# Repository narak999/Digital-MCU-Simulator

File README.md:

# Digital-MCU-Simulator
This is the project for ECEN 403 and ECEN 404 class.

For my code (DMCUS_IDE.py), in order to successfully run it, the user will need to change the directories inside the code. The user will also need to install some Python packages including Pygments, Tkinter, Signal, Subprocess, and Webbrowser. One more thing that might prevent the code from running on the user's computer might be the location of the icon file cannot be located, although the icon file is attached with the code above. 

simavr was created by Michel Polet under the GNU GPL 3.0 licensing. His github can be found here:
https://github.com/buserror/simavr

NOTE: This Python code is created and meant to run with Python 3.6. Using a different version of Python to compile and run the code might cause unexpected errors.

Compilation command for simavr: 

avr-gcc -Wall -gdwarf-2 -Os -std=gnu99 -DF_CPU=8000000 -fno-inline-small-functions -ffunction-sections -fdata-sections -Wl,--relax,--gc-sections -Wl,--undefined=_mmcu,--section-start=.mmcu=0x910000 -I ~/Desktop/simavr/simavr/sim -I ~/Desktop/simavr/simavr/sim/avr -mmcu=atmega88 ledblink.c -o ledblink.elf

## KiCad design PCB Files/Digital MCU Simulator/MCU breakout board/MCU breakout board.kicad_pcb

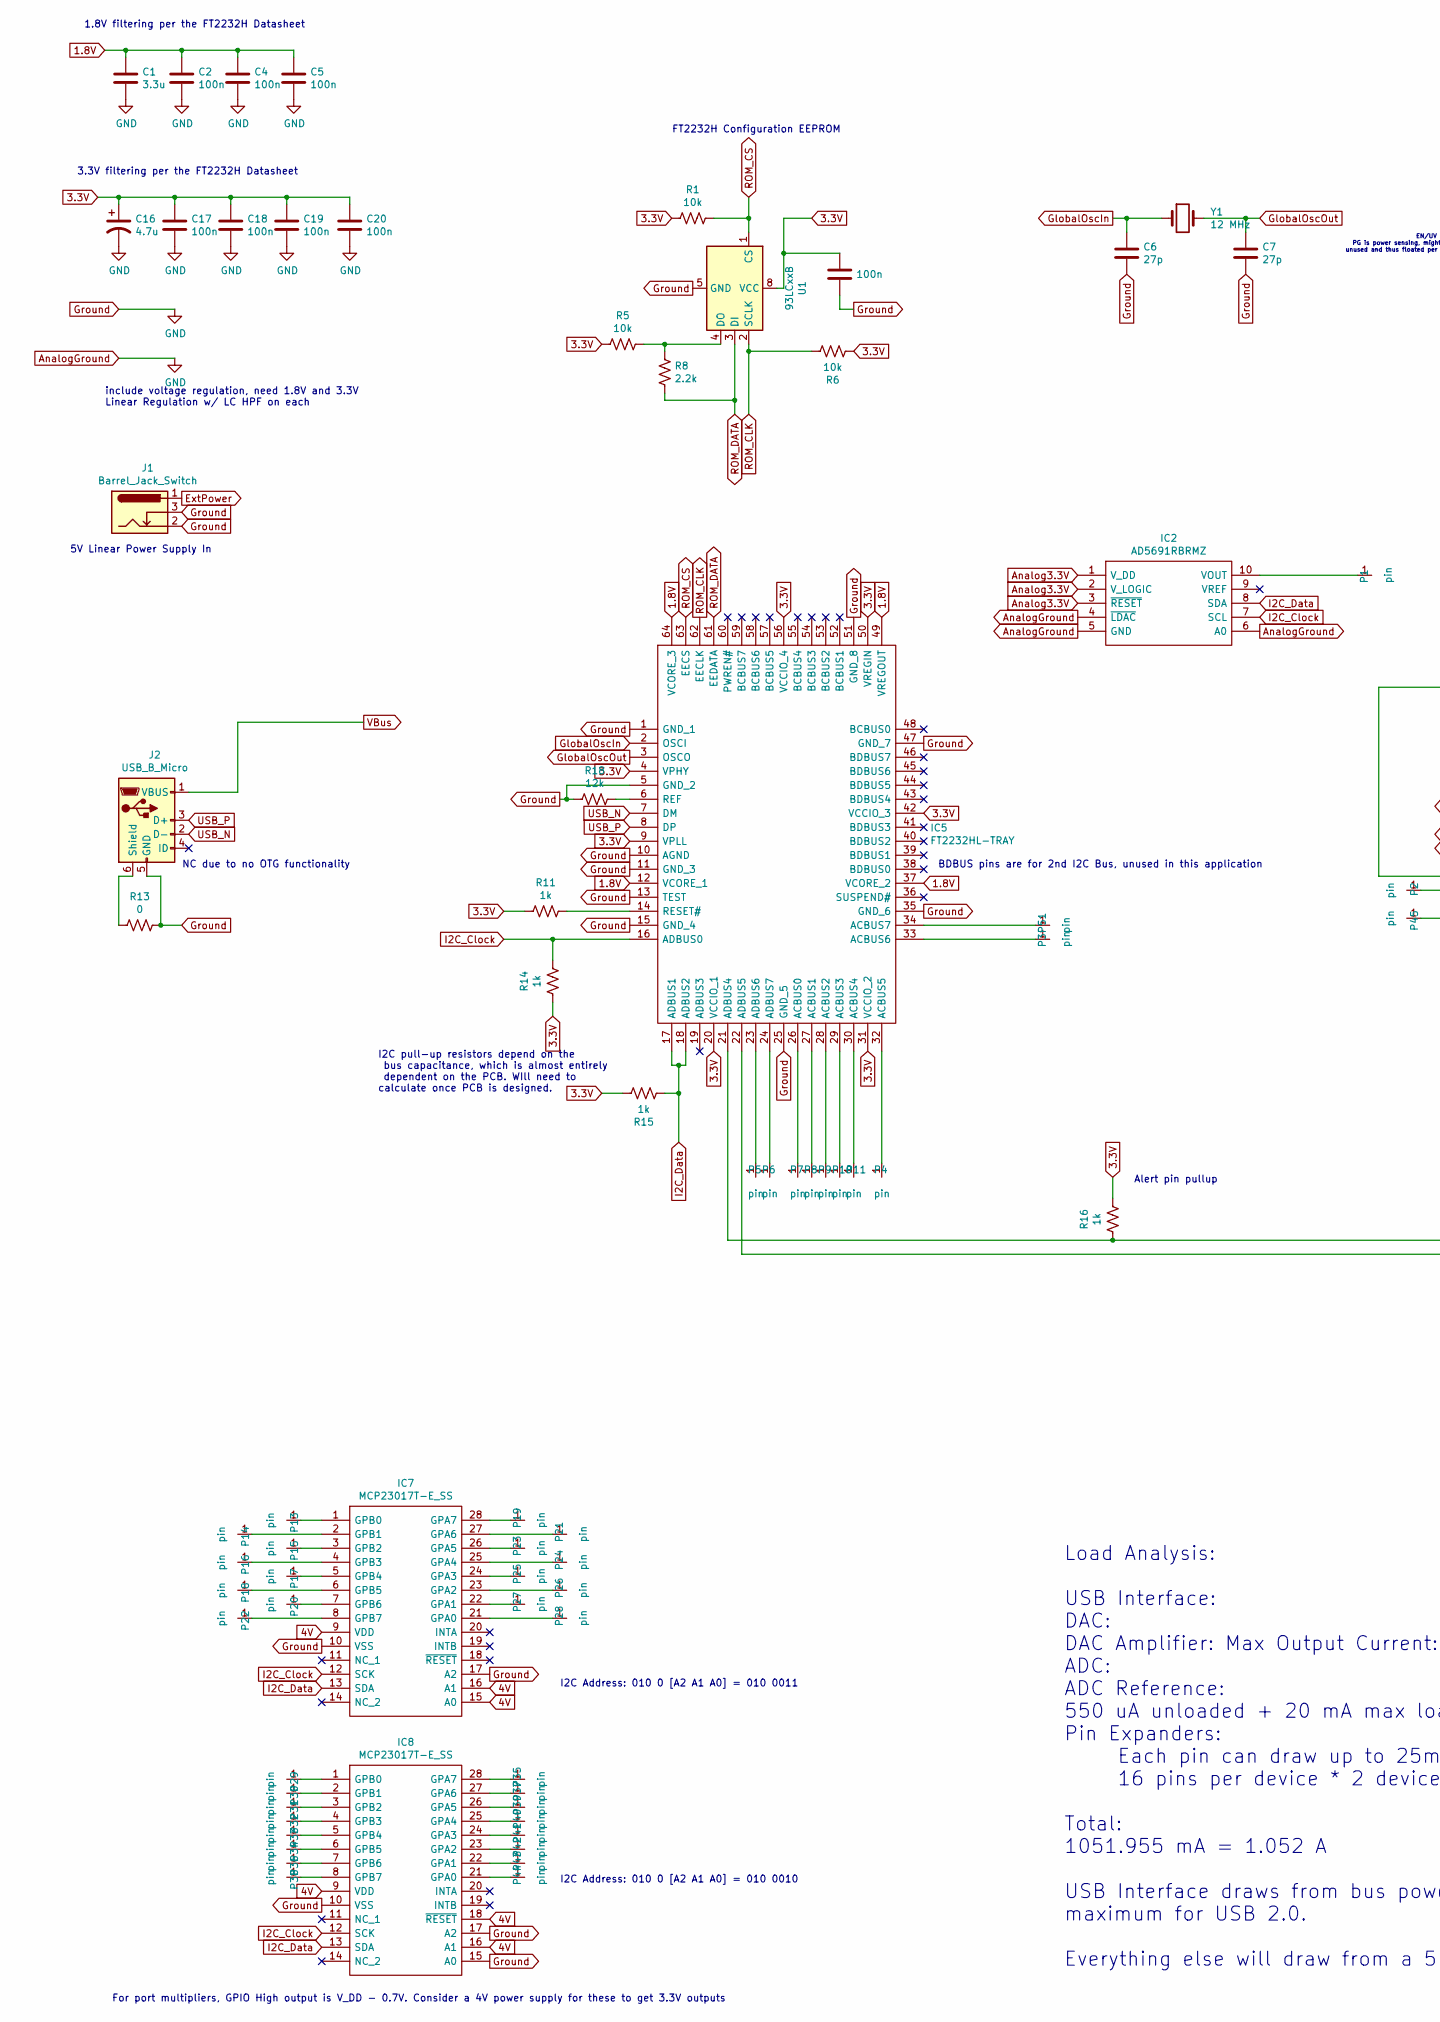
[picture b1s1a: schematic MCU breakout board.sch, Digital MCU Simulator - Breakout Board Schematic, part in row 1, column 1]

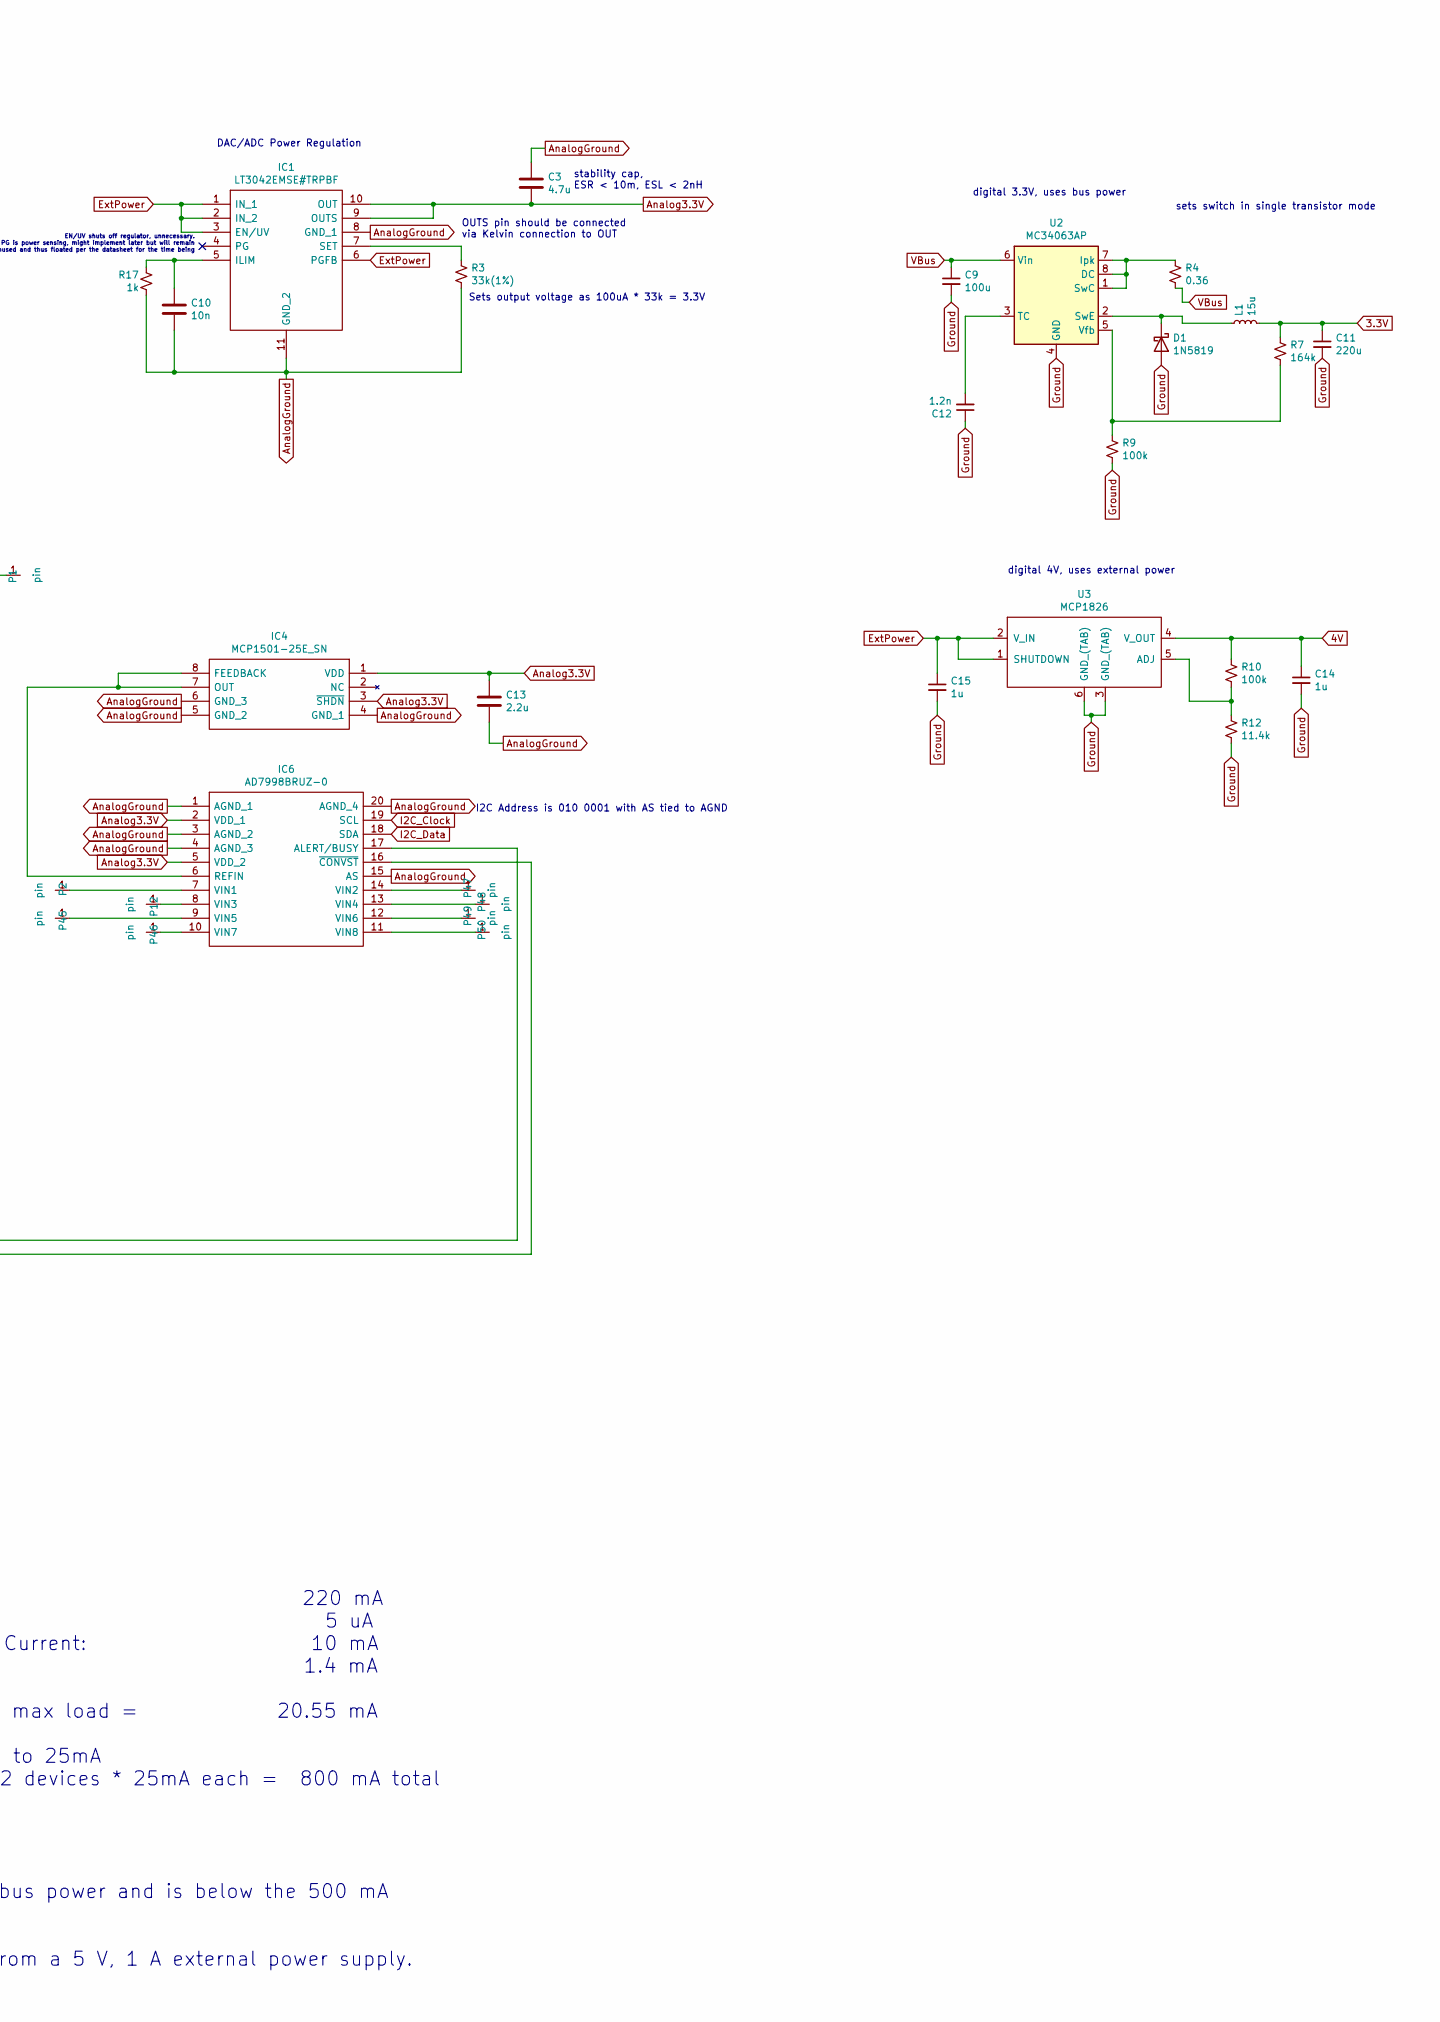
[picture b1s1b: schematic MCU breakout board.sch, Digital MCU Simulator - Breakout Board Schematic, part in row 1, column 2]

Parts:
C1: 3.3u; C_0805_2012Metric
C2, C4, C5, C8, C17, C18, C19, C20: 100n; C_0805_2012Metric
C3: 4.7u; C_0805_2012Metric
C6, C7: 27p; C_0805_2012Metric
C9: 100u; C_0805_2012Metric
C10: 10n; C_0805_2012Metric
C11: 220u; C_1210_3225Metric
C12: 1.2n; C_0805_2012Metric
C13: 2.2u; C_0805_2012Metric
C14, C15: 1u; C_0805_2012Metric
C16: 4.7u; CP_Elec_6.3x5.8
D1: 1N5819; D_DO-41_SOD81_P10.16mm_Horizontal
IC1: LT3042EMSE#TRPBF; SOP50P490X110-11N; Mouser Part Number 584-LT3042EMSE#TRPBF
IC2: AD5691RBRMZ; SOP50P490X110-10N; Manufacturer_Part_Number AD5691RBRMZ
IC4: MCP1501-25E_SN; SOIC127P600X175-8N; Mouser Part Number 579-MCP1501-25E/SN
IC5: FT2232HL-TRAY; QFP50P1200X1200X160-64N; Mouser Part Number 895-FT2232HL-TRAY
IC6: AD7998BRUZ-0; SOP65P640X120-20N; Mouser Part Number 584-AD7998BRUZ-0
IC7, IC8: MCP23017T-E_SS; SOP65P780X200-28N; Mouser Part Number 579-MCP23017T-E/SS
J1: Barrel_Jack_Switch; BarrelJack_CUI_PJ-102AH_Horizontal
J2: USB_B_Micro; USB_Micro-B_Molex-105017-0001
L1: 15u; L_1812_4532Metric
P1, P2, P3, P4, P5, P6, P7, P8, P9, P10, P11, P12, P13, P14, P15, P16, P17, P18, P19, P20, P21, P22, P23, P24, P25, P26, P27, P28, P29, P30, P31, P32, P33, P34, P35, P36, P37, P38, P39, P40, P41, P42, P43, P44, P45, P46, P47, P48, P49, P50, P51: pin; PinHeader_1x01_P2.54mm_Vertical
R1, R5, R6: 10k; R_0805_2012Metric
R3: 33k(1%); R_0805_2012Metric
R4: 0.36; R_0805_2012Metric
R7: 164k; R_0805_2012Metric
R8: 2.2k; R_0805_2012Metric
R9, R10: 100k; R_0805_2012Metric
R11, R14, R15, R16, R17: 1k; R_0805_2012Metric
R12: 11.4k; R_0805_2012Metric
R13: 0; R_0805_2012Metric
R18: 12k; R_0805_2012Metric
U1: 93LCxxB; SOIC-8_3.9x4.9mm_P1.27mm
U2: MC34063AP; DIP-8_W7.62mm
U3: MCP1826; TO-220-5_Horizontal_TabDown_tab_pin_6
Y1: 12 MHz; Crystal_HC49-U_Vertical

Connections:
1.8V: C1.1, C2.1, C4.1, C5.1, IC5.12 (VCORE_1), IC5.37 (VCORE_2), IC5.49 (VREGOUT), IC5.64 (VCORE_3)
3.3V: C8.1, C11.1, C16.1, C17.1, C18.1, C19.1, C20.1, IC5.4 (VPHY), IC5.9 (VPLL), IC5.20 (VCCIO_1), IC5.31 (VCCIO_2), IC5.42 (VCCIO_3), IC5.50 (VREGIN), IC5.56 (VCCIO_4), L1.2, R1.2, R5.2, R6.2, R7.1, R11.2, R14.2, R15.1, R16.1, U1.8 (VCC)
4V: C14.1, IC7.9 (VDD), IC7.15 (A0), IC7.16 (A1), IC8.9 (VDD), IC8.16 (A1), IC8.18 (~RESET), R10.1, U3.4 (V_OUT)
Analog3.3V: C3.2, C13.1, IC1.9 (OUTS), IC1.10 (OUT), IC2.1 (V_DD), IC2.2 (V_LOGIC), IC2.3 (~RESET), IC4.1 (VDD), IC4.3 (~SHDN), IC6.2 (VDD_1), IC6.5 (VDD_2)
AnalogGround: C1.2, C2.2, C3.1, C4.2, C5.2, C6.2, C7.2, C8.2, C9.2, C10.2, C11.2, C12.1, C13.2, C14.2, C15.2, C16.2, C17.2, C18.2, C19.2, C20.2, D1.2 (A), IC1.8 (GND_1), IC1.11 (GND_2), IC2.4 (~LDAC), IC2.5 (GND), IC2.6 (A0), IC4.4 (GND_1), IC4.5 (GND_2), IC4.6 (GND_3), IC5.1 (GND_1), IC5.5 (GND_2), IC5.10 (AGND), IC5.11 (GND_3), IC5.13 (TEST), IC5.15 (GND_4), IC5.25 (GND_5), IC5.35 (GND_6), IC5.47 (GND_7), IC5.51 (GND_8), IC6.1 (AGND_1), IC6.3 (AGND_2), IC6.4 (AGND_3), IC6.15 (AS), IC6.20 (AGND_4), IC7.10 (VSS), IC7.17 (A2), IC8.10 (VSS), IC8.15 (A0), IC8.17 (A2), J1.2, J1.3, J2.5 (GND), R3.2, R9.2, R12.2, R13.1, R17.2, R18.2, U1.5 (GND), U2.4 (GND), U3.3 (GND_(TAB)), U3.6 (GND_(TAB)); also elsewhere on the board
ExtPower: C15.1, IC1.1 (IN_1), IC1.2 (IN_2), IC1.3 (EN/UV), IC1.6 (PGFB), J1.1, U3.1 (SHUTDOWN), U3.2 (V_IN); also elsewhere on the board
GlobalOscIn: C6.1, IC5.2 (OSCI), Y1.1
GlobalOscOut: C7.1, IC5.3 (OSCO), Y1.2
I2C_Clock: IC2.7 (SCL), IC5.16 (ADBUS0), IC6.19 (SCL), IC7.12 (SCK), IC8.12 (SCK), R14.1
I2C_Data: IC2.8 (SDA), IC5.17 (ADBUS1), IC5.18 (ADBUS2), IC6.18 (SDA), IC7.13 (SDA), IC8.13 (SDA), R15.2
unnamed: C10.1, IC1.5 (ILIM), R17.1
unnamed: C12.2, U2.3 (TC)
unnamed: D1.1 (K), L1.1, U2.2 (SwE)
unnamed: IC1.7 (SET), R3.1
unnamed: IC2.10 (VOUT), P1.1
unnamed: IC4.7 (OUT), IC4.8 (FEEDBACK), IC6.6 (REFIN)
unnamed: IC5.6 (REF), R18.1
unnamed: IC5.14 (RESET#), R11.1
unnamed: IC5.21 (ADBUS4), IC6.17 (ALERT/BUSY), R16.2
unnamed: IC5.22 (ADBUS5), IC6.16 (~CONVST)
unnamed: IC5.23 (ADBUS6), P5.1
unnamed: IC5.24 (ADBUS7), P6.1
unnamed: IC5.26 (ACBUS0), P7.1
unnamed: IC5.27 (ACBUS1), P8.1
unnamed: IC5.28 (ACBUS2), P9.1
unnamed: IC5.29 (ACBUS3), P10.1
unnamed: IC5.30 (ACBUS4), P11.1
unnamed: IC5.32 (ACBUS5), P4.1
unnamed: IC5.33 (ACBUS6), P3.1
unnamed: IC5.34 (ACBUS7), P51.1
unnamed: IC6.7 (VIN1), P2.1
unnamed: IC6.8 (VIN3), P12.1
unnamed: IC6.9 (VIN5), P45.1
unnamed: IC6.10 (VIN7), P46.1
unnamed: IC6.11 (VIN8), P50.1
unnamed: IC6.12 (VIN6), P49.1
unnamed: IC6.13 (VIN4), P48.1
unnamed: IC6.14 (VIN2), P47.1
unnamed: IC7.1 (GPB0), P13.1
unnamed: IC7.2 (GPB1), P14.1
unnamed: IC7.3 (GPB2), P15.1
unnamed: IC7.4 (GPB3), P16.1
unnamed: IC7.5 (GPB4), P17.1
unnamed: IC7.6 (GPB5), P18.1
unnamed: IC7.7 (GPB6), P20.1
unnamed: IC7.8 (GPB7), P22.1
unnamed: IC7.21 (GPA0), P28.1
unnamed: IC7.22 (GPA1), P27.1
unnamed: IC7.23 (GPA2), P26.1
unnamed: IC7.24 (GPA3), P25.1
unnamed: IC7.25 (GPA4), P24.1
unnamed: IC7.26 (GPA5), P23.1
unnamed: IC7.27 (GPA6), P21.1
unnamed: IC7.28 (GPA7), P19.1
unnamed: IC8.1 (GPB0), P29.1
unnamed: IC8.2 (GPB1), P30.1
unnamed: IC8.3 (GPB2), P31.1
unnamed: IC8.4 (GPB3), P32.1
unnamed: IC8.5 (GPB4), P33.1
unnamed: IC8.6 (GPB5), P34.1
unnamed: IC8.7 (GPB6), P36.1
unnamed: IC8.8 (GPB7), P38.1
unnamed: IC8.21 (GPA0), P44.1
unnamed: IC8.22 (GPA1), P43.1
unnamed: IC8.23 (GPA2), P42.1
unnamed: IC8.24 (GPA3), P41.1
unnamed: IC8.25 (GPA4), P40.1
unnamed: IC8.26 (GPA5), P39.1
unnamed: IC8.27 (GPA6), P37.1
unnamed: IC8.28 (GPA7), P35.1
unnamed: J2.6 (Shield), R13.2
unnamed: R4.1, U2.1 (SwC), U2.7 (Ipk), U2.8 (DC)
unnamed: R5.1, R8.2, U1.4 (DO)
unnamed: R7.2, R9.1, U2.5 (Vfb)
unnamed: R10.2, R12.1, U3.5 (ADJ)
ROM_CLK: IC5.62 (EECLK), R6.1, U1.2 (SCLK)
ROM_CS: IC5.63 (EECS), R1.1, U1.1 (CS)
ROM_DATA: IC5.61 (EEDATA), R8.1, U1.3 (DI)
USB_N: IC5.7 (DM), J2.2 (D-)
USB_P: IC5.8 (DP), J2.3 (D+)
VBus: C9.1, J2.1 (VBUS), R4.2, U2.6 (Vin)

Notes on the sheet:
include voltage regulation, need 1.8V and 3.3V Linear Regulation w/ LC HPF on each
1.8V filtering per the FT2232H Datasheet
FT2232H Configuration EEPROM
I2C Address is 010 0001 with AS tied to AGND
For port multipliers, GPIO High output is V_DD - 0.7V. Consider a 4V power supply for these to get 3.3V outputs
Load Analysis: USB Interface: 220 mA DAC: 5 uA DAC Amplifier: Max Output Current: 10 mA ADC: 1.4 mA ADC Reference: 550 uA unloaded + 20 mA max load = 20.55 mA Pin Expanders: Each pin can draw up to 25mA 16 pins per device * 2 devices * 25mA each = 800 mA total Total: 1051.955 mA = 1.052 A USB Inter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
DAC/ADC Power Regulation
5V Linear Power Supply In
Sets output voltage as 100uA * 33k = 3.3V
OUTS pin should be connected via Kelvin connection to OUT
EN/UV shuts off regulator, unnecessary. PG is power sensing, might implement later but will remain unused and thus floated per the datasheet for the time being
stability cap, ESR < 10m, ESL < 2nH
digital 3.3V, uses bus power
sets switch in single transistor mode
digital 4V, uses external power
I2C pull-up resistors depend on the bus capacitance, which is almost entirely dependent on the PCB. WIll need to calculate once PCB is designed.
BDBUS pins are for 2nd I2C Bus, unused in this application
Alert pin pullup
I2C Address: 010 0 [A2 A1 A0] = 010 0010
I2C Address: 010 0 [A2 A1 A0] = 010 0011
3.3V filtering per the FT2232H Datasheet
NC due to no OTG functionality

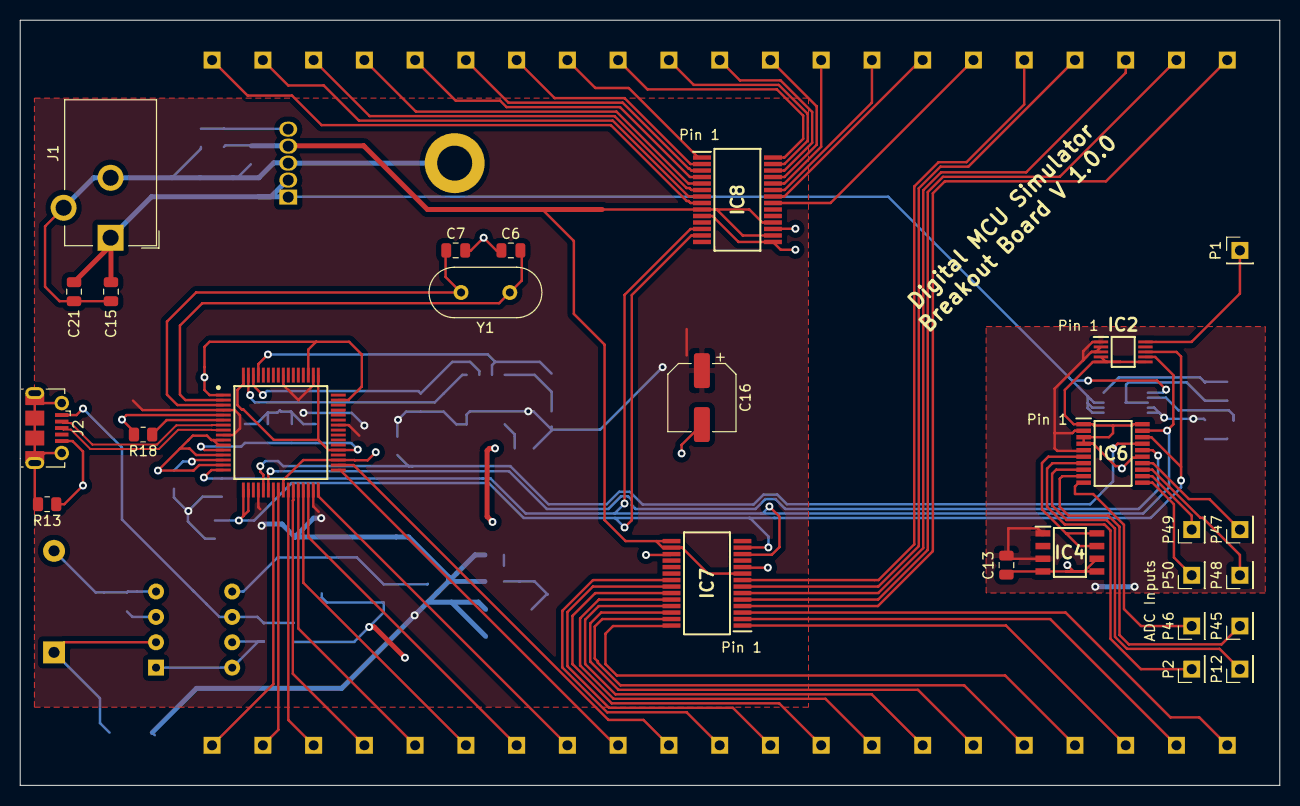
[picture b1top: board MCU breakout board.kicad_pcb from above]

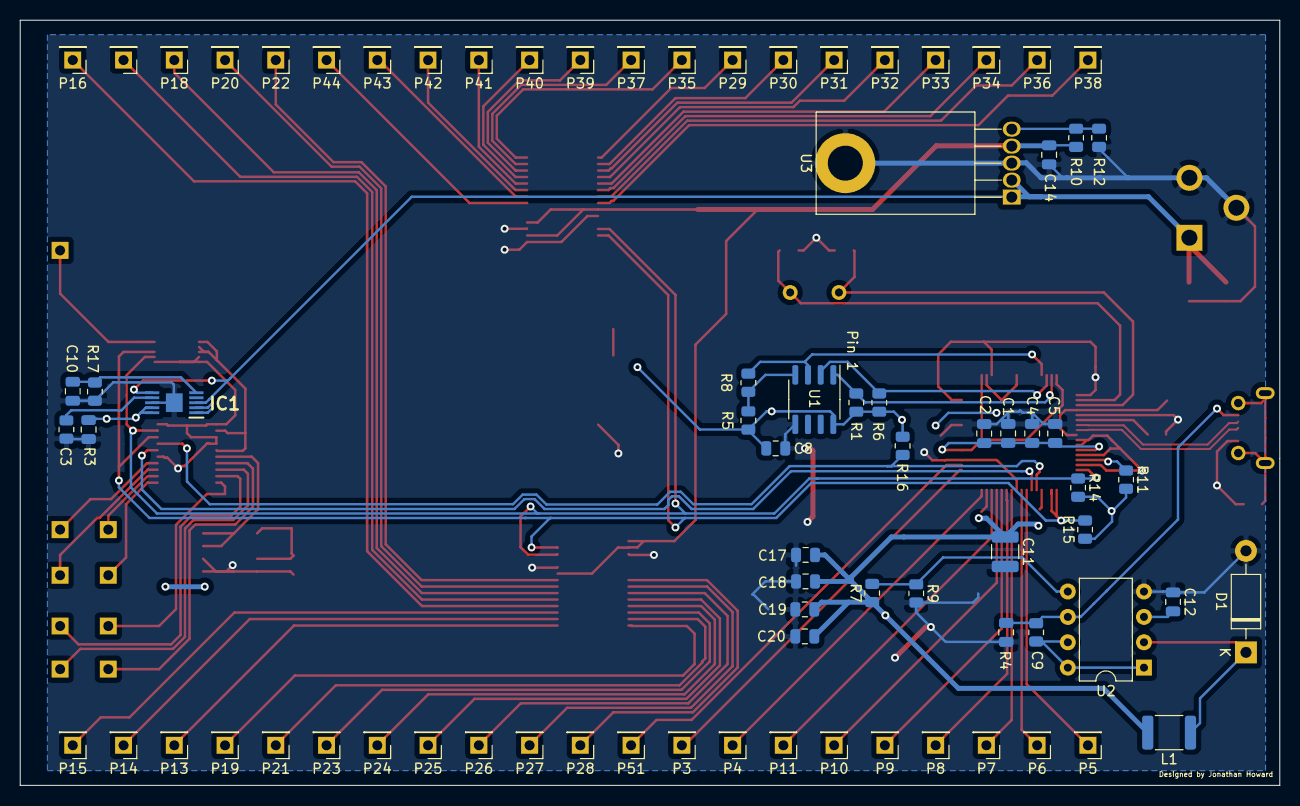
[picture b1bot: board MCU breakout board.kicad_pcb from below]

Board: 2 copper layers, 126.1 x 76.6 mm, 104 parts (78 on the bottom side), 81 nets.

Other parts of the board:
C21: 100p; C_0805_2012Metric

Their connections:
AnalogGround: C21.2; also elsewhere on the board
ExtPower: C21.1; also elsewhere on the board

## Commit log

2020-11-23 Add files via upload
    Some changes will need to be made to the code, i.e. the directory mentioned in the code, the location of the icon file etc.
2020-11-25 Added PCB Files
2021-03-03 Test Code and Programmers Guides for USB Interface
2021-03-03 Folder Rename
    Renamed "Test" to "Hardware Test" to better reflect the contents
2021-03-13 Update to test code
    Filled out the code for writing and reading to various devices as well as on-start initialization. Working on configuration of FT2232HL and rewriting sample code to avoid potential licensing concerns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
2021-03-21 switching to linux
    here's what I've got so far
2021-04-13 open terminal in linux
2021-04-13 checking to see where terminal opens up
2021-04-13 compiled
2021-04-13 terminal command includes bash
2021-04-13 sends output to out folder
2021-04-17 Adding new files from Linux. I hate CLI git
2021-04-17 updated ledblink.c to work with simavr
2021-04-19 fixed .end bug
2021-04-20 Deleted LibMPSSE source code, was causing issues with GitHub GUI on
2021-04-20 Pre Demo Commit
2021-04-20 Pre Demo Update
2021-04-20 Create bin
2021-04-21 Updated simavr
2021-04-21 Added modified simavr to project
2021-04-21 ECEN 404 Demo Feedback doc
2021-04-21 adding ECEN 404 team feedback
2021-04-21 added udev rule to allow the board to work with the program
2021-04-21 Rename README.txt to README.cmd
2021-04-21 Rename README.cmd to README.md
2021-04-21 adding licenses to modified files
2021-04-21 Final Demo Update
2021-04-21 fixed buttons, fixed plotting error
2021-04-21 all nodes show up now
2021-04-21 added ~/
